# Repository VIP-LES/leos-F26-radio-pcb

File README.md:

# LEOS Radio PCB

This repository contains the KiCad schematic and PCB layout for the LEOS Radio PCB made fall 2026. The board integrates a Raspberry Pi Pico, an E22-900M30S LoRa radio module, and a CAN-FD interface.

The Raspberry Pi Pico communicates with the radio module through SPI1 and the MCP2518FD CAN-FD controller through SPI0. An MCP2562FD transceiver connects the CAN controller to the LEOS CAN bus. An SMA connector provides the connection for an external antenna.

## Board Overview
Main hardware functions:
- Wireless communication: E22-900M30S LoRa radio module provides wireless transmission and reception through an external antenna connected to the SMA connector.
- CAN-FD communication: MCP2518FD controller and MCP2562FD transceiver provide the interface to the LEOS CAN bus.
- Microcontroller control: Pico interfaces with the radio module and CAN controller through separate SPI buses. Additional GPIO connections provide radio reset, busy monitoring, interrupt, and receive-enable signals.

## Electrical Design
- Board supply: 5 V
- Microcontroller: Raspberry Pi Pico, as labeled in the schematic
- Radio module: E22-900M30S
- CAN-FD controller: MCP2518FD
- CAN-FD transceiver: MCP2562FD
- Bus connectors: Two four-pin MicroFit connectors

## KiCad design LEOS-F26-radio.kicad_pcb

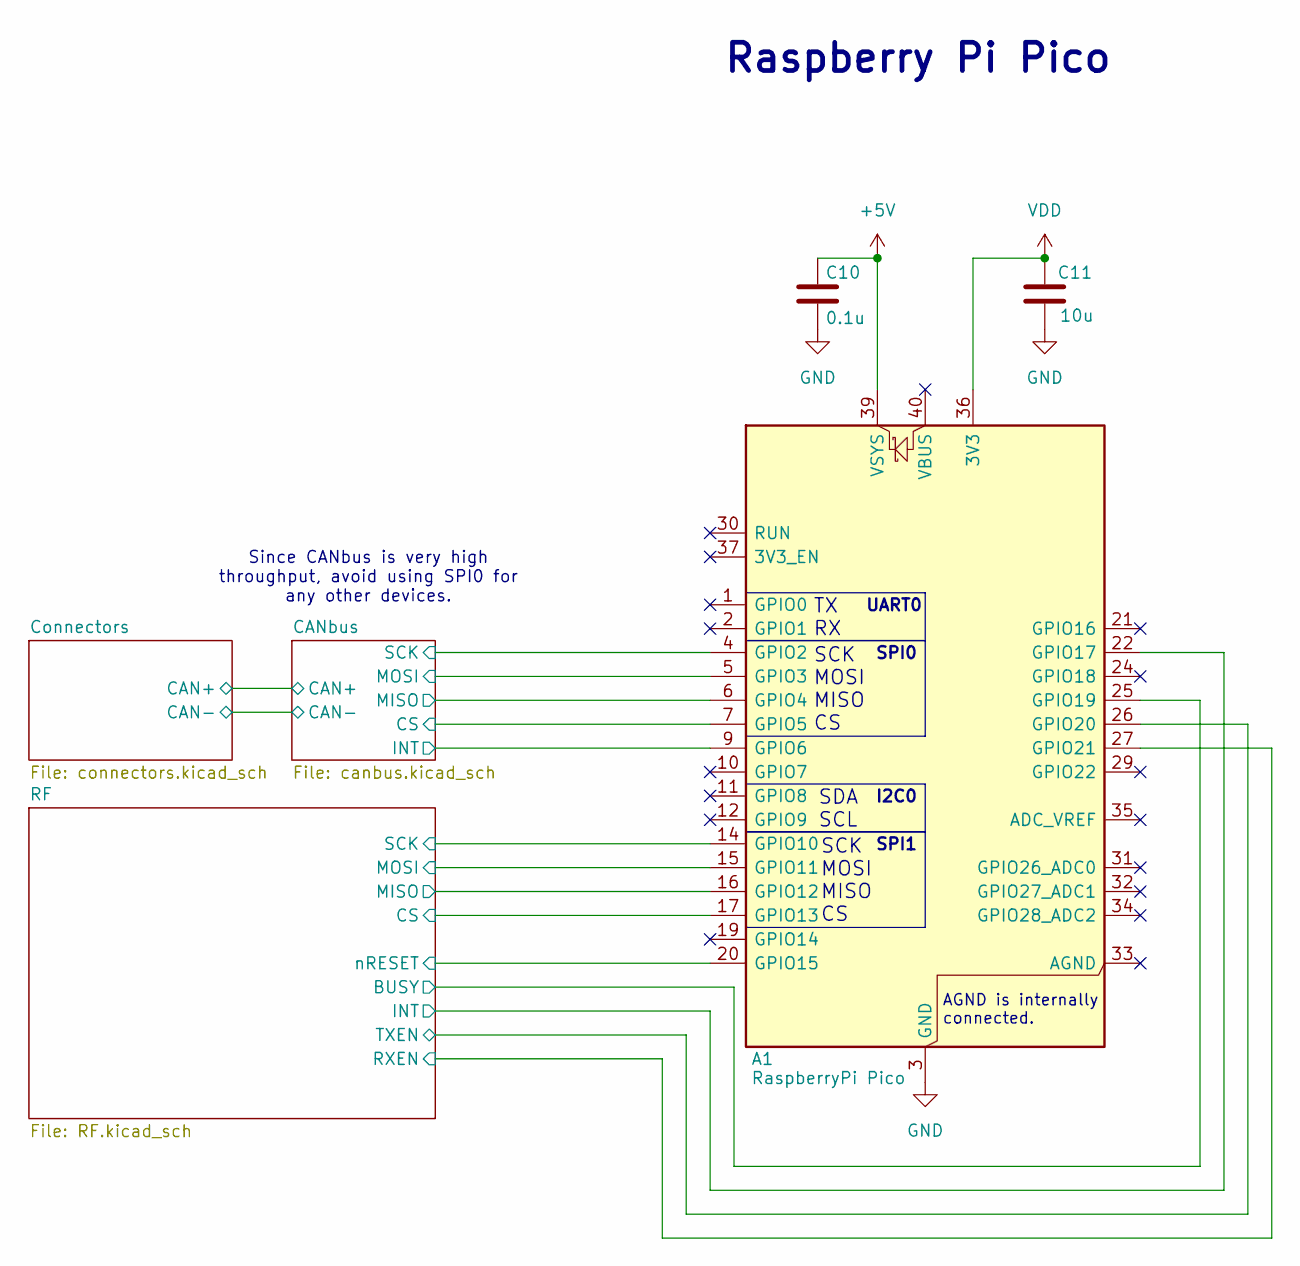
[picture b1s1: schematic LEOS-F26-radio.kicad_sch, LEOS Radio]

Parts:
A1: RaspberryPi Pico; RaspberryPi_Pico_Common_Unspecified; MPN PIM724; Digikey 1778-PIM724-ND
C10: 0.1u; C_0805_2012Metric; MPN CL21B104KBCNNNC; Digikey 1276-1003-1-ND
C11: 10u; C_0805_2012Metric; MPN CL21B106KOQNNNE; Digikey 1276-2872-1-ND

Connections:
+5V: A1.39 (VSYS), C10.1; also elsewhere on the board
/CANbus/CS: A1.7 (GPIO5); also elsewhere on the board
/CANbus/INT: A1.9 (GPIO6); also elsewhere on the board
/CANbus/MISO: A1.6 (GPIO4); also elsewhere on the board
/CANbus/MOSI: A1.5 (GPIO3); also elsewhere on the board
/CANbus/SCK: A1.4 (GPIO2); also elsewhere on the board
/RF/BUSY: A1.25 (GPIO19); also elsewhere on the board
/RF/CS: A1.17 (GPIO13); also elsewhere on the board
/RF/INT: A1.22 (GPIO17); also elsewhere on the board
/RF/MISO: A1.16 (GPIO12); also elsewhere on the board
/RF/MOSI: A1.15 (GPIO11); also elsewhere on the board
/RF/RXEN: A1.27 (GPIO21); also elsewhere on the board
/RF/SCK: A1.14 (GPIO10); also elsewhere on the board
/RF/TXEN: A1.26 (GPIO20); also elsewhere on the board
/RF/nRESET: A1.20 (GPIO15); also elsewhere on the board
GND: A1.3 (GND), A1.8 (GND), A1.13 (GND), A1.18 (GND), A1.23 (GND), A1.28 (GND), A1.38 (GND), C10.2, C11.2; also elsewhere on the board
VDD: A1.36 (3V3), C11.1; also elsewhere on the board

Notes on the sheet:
SPI1
Raspberry Pi Pico
SCK MOSI MISO CS
Since CANbus is very high throughput, avoid using SPI0 for any other devices.
SPI0
SDA SCL
TX RX
UART0
I2C0
AGND is internally connected.

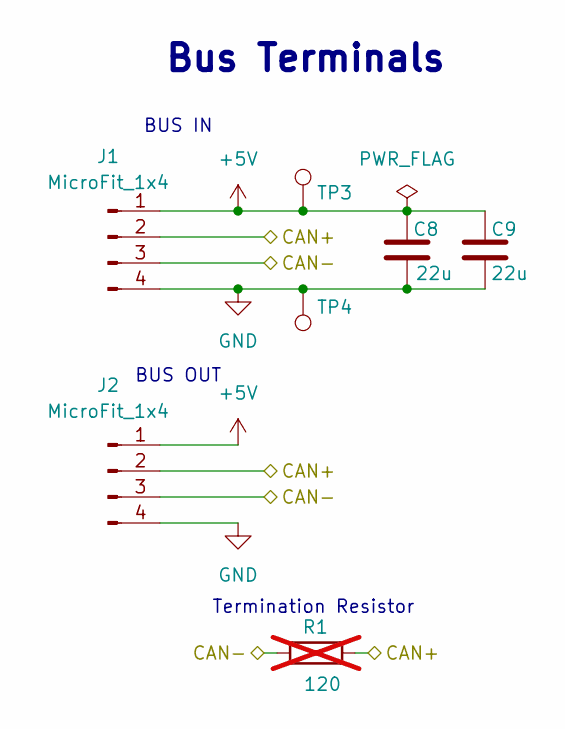
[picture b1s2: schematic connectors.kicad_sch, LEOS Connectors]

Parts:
C8, C9: 22u; C_1206_3216Metric; MPN CL31B226MPHNNNE; Digikey 1276-3148-1-ND
J1, J2: MicroFit_1x4; Molex_MicroFit3.0_43650-0410_1x04_Horizontal; MPN 0436500409; Digikey WM1882CT-ND
R1: 120; R_Axial_DIN0207_L6.3mm_D2.5mm_P7.62mm_Horizontal; MPN CF14JT120R; Digikey CF14JT120RCT-ND; not fitted
TP3: 5V Test Point; TestPoint_Loop_D2.60mm_Drill0.9mm_Beaded; MPN 5000; Digikey 36-5000-ND
TP4: GND Test Point; TestPoint_Loop_D2.60mm_Drill0.9mm_Beaded; MPN 5001; Digikey 36-5001-ND

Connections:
+5V: C8.1, C9.1, J1.1, J2.1, TP3.1 (1_1); also elsewhere on the board
/CANbus/CAN+: J1.2, J2.2, R1.2; also elsewhere on the board
/CANbus/CAN-: J1.3, J2.3, R1.1; also elsewhere on the board
GND: C8.2, C9.2, J1.4, J2.4, TP4.1 (1_1); also elsewhere on the board

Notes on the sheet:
BUS OUT
Bus Terminals
BUS IN
Termination Resistor

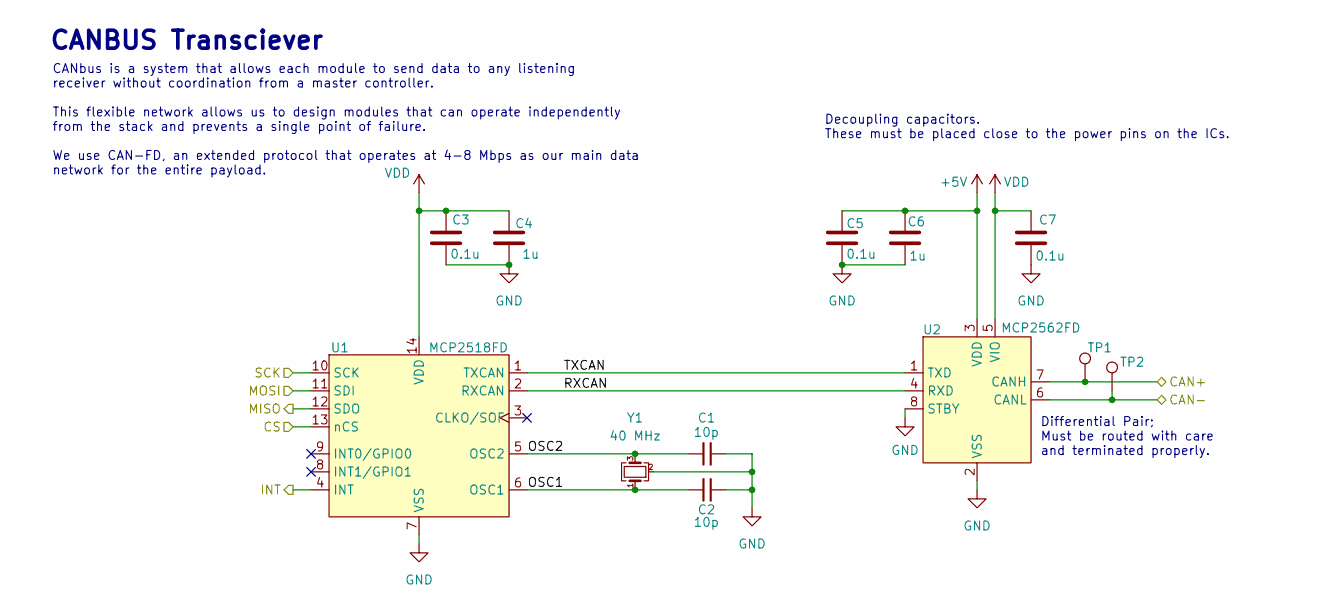
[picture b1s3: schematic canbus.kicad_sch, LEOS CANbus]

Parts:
C1, C2: 10p; C_0805_2012Metric; MPN CL21C100CBANNNC; Digikey 1276-2561-1-ND
C3, C5, C7: 0.1u; C_0805_2012Metric; MPN CL21B104KBCNNNC; Digikey 1276-1003-1-ND
C4, C6: 1u; C_0805_2012Metric; MPN C0805C105K3RACTU; Digikey 399-C0805C105K3RACTUCT-ND
TP1: CAN-H Test Point; TestPoint_Loop_D2.60mm_Drill0.9mm_Beaded; MPN 5004; Digikey 36-5004-ND
TP2: CAN-L Test Point; TestPoint_Loop_D2.60mm_Drill0.9mm_Beaded; MPN 5116; Digikey 36-5116-ND
U1: MCP2518FD; SOIC-14_3.9x8.7mm_P1.27mm; MPN MCP2518FDT-E/SL; LCSC C626758
U2: MCP2562FD; SOIC-8_3.9x4.9mm_P1.27mm; MPN MCP2562FDT-H/SN; LCSC C511335
Y1: 40 MHz; Crystal_SMD_2016-4Pin_2.0x1.6mm; MPN ECS-400-10-37B2-CKY-TR; Digikey 50-ECS-400-10-37B2-CKY-TRCT-ND

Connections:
+5V: C5.1, C6.1, U2.3 (VDD); also elsewhere on the board
/CANbus/CAN+: TP1.1 (1_1), U2.7 (CANH); also elsewhere on the board
/CANbus/CAN-: TP2.1 (1_1), U2.6 (CANL); also elsewhere on the board
/CANbus/CS: U1.13 (nCS); also elsewhere on the board
/CANbus/INT: U1.4 (INT); also elsewhere on the board
/CANbus/MISO: U1.12 (SDO); also elsewhere on the board
/CANbus/MOSI: U1.11 (SDI); also elsewhere on the board
/CANbus/OSC1: C2.2, U1.6 (OSC1), Y1.1
/CANbus/OSC2: C1.2, U1.5 (OSC2), Y1.3
/CANbus/RXCAN: U1.2 (RXCAN), U2.4 (RXD)
/CANbus/SCK: U1.10 (SCK); also elsewhere on the board
/CANbus/TXCAN: U1.1 (TXCAN), U2.1 (TXD)
GND: C1.1, C2.1, C3.2, C4.2, C5.2, C6.2, C7.2, U1.7 (VSS), U2.2 (VSS), U2.8 (STBY), Y1.2 (G), Y1.4 (G); also elsewhere on the board
VDD: C3.1, C4.1, C7.1, U1.14 (VDD), U2.5 (VIO); also elsewhere on the board

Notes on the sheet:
Differential Pair; Must be routed with care and terminated properly.
CANBUS Transciever
CANbus is a system that allows each module to send data to any listening receiver without coordination from a master controller. This flexible network allows us to design modules that can operate independently from the stack and prevents a single point of failure. We use CAN-FD, an extended protoco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
Decoupling capacitors. These must be placed close to the power pins on the ICs.

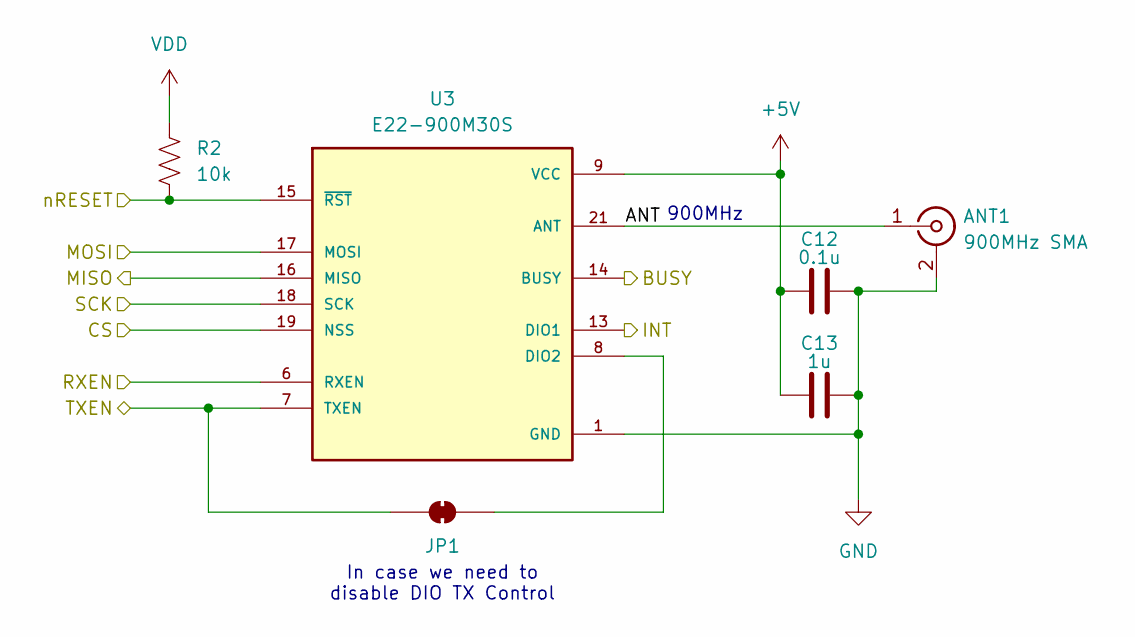
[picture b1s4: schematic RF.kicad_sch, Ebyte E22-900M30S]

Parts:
ANT1: 900MHz SMA; SMA_Molex_73251-1153_EdgeMount_Horizontal; MPN 0732511153; Digikey 900-0732511153-ND
C12: 0.1u; C_0805_2012Metric; MPN CL21B104KBCNNNC; Digikey 1276-1003-1-ND
C13: 1u; C_0805_2012Metric; MPN C0805C105K3RACTU; Digikey 399-C0805C105K3RACTUCT-ND
JP1: SolderJumper_2_Bridged; SolderJumper-2_P1.3mm_Bridged_RoundedPad1.0x1.5mm
R2: 10k; R_0805_2012Metric; MPN CRCW080510K0FKEA; Digikey 541-10.0KCCT-ND
U3: E22-900M30S; XCVR_E22-900M30S

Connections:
+5V: C12.1, C13.1, U3.9 (VCC), U3.10 (VCC); also elsewhere on the board
/RF/ANT: ANT1.1 (In), U3.21 (ANT)
/RF/BUSY: U3.14 (BUSY); also elsewhere on the board
/RF/CS: U3.19 (NSS); also elsewhere on the board
/RF/INT: U3.13 (DIO1); also elsewhere on the board
/RF/MISO: U3.16 (MISO); also elsewhere on the board
/RF/MOSI: U3.17 (MOSI); also elsewhere on the board
/RF/RXEN: U3.6 (RXEN); also elsewhere on the board
/RF/SCK: U3.18 (SCK); also elsewhere on the board
/RF/TXEN: JP1.1 (A), U3.7 (TXEN); also elsewhere on the board
/RF/nRESET: R2.2, U3.15 (~RST); also elsewhere on the board
GND: ANT1.2 (Ext), C12.2, C13.2, U3.1 (GND), U3.2 (GND), U3.3 (GND), U3.4 (GND), U3.5 (GND), U3.11 (GND), U3.12 (GND), U3.20 (GND), U3.22 (GND); also elsewhere on the board
unnamed: JP1.2 (B), U3.8 (DIO2)
VDD: R2.1; also elsewhere on the board

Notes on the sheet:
In case we need to disable DIO TX Control
900MHz

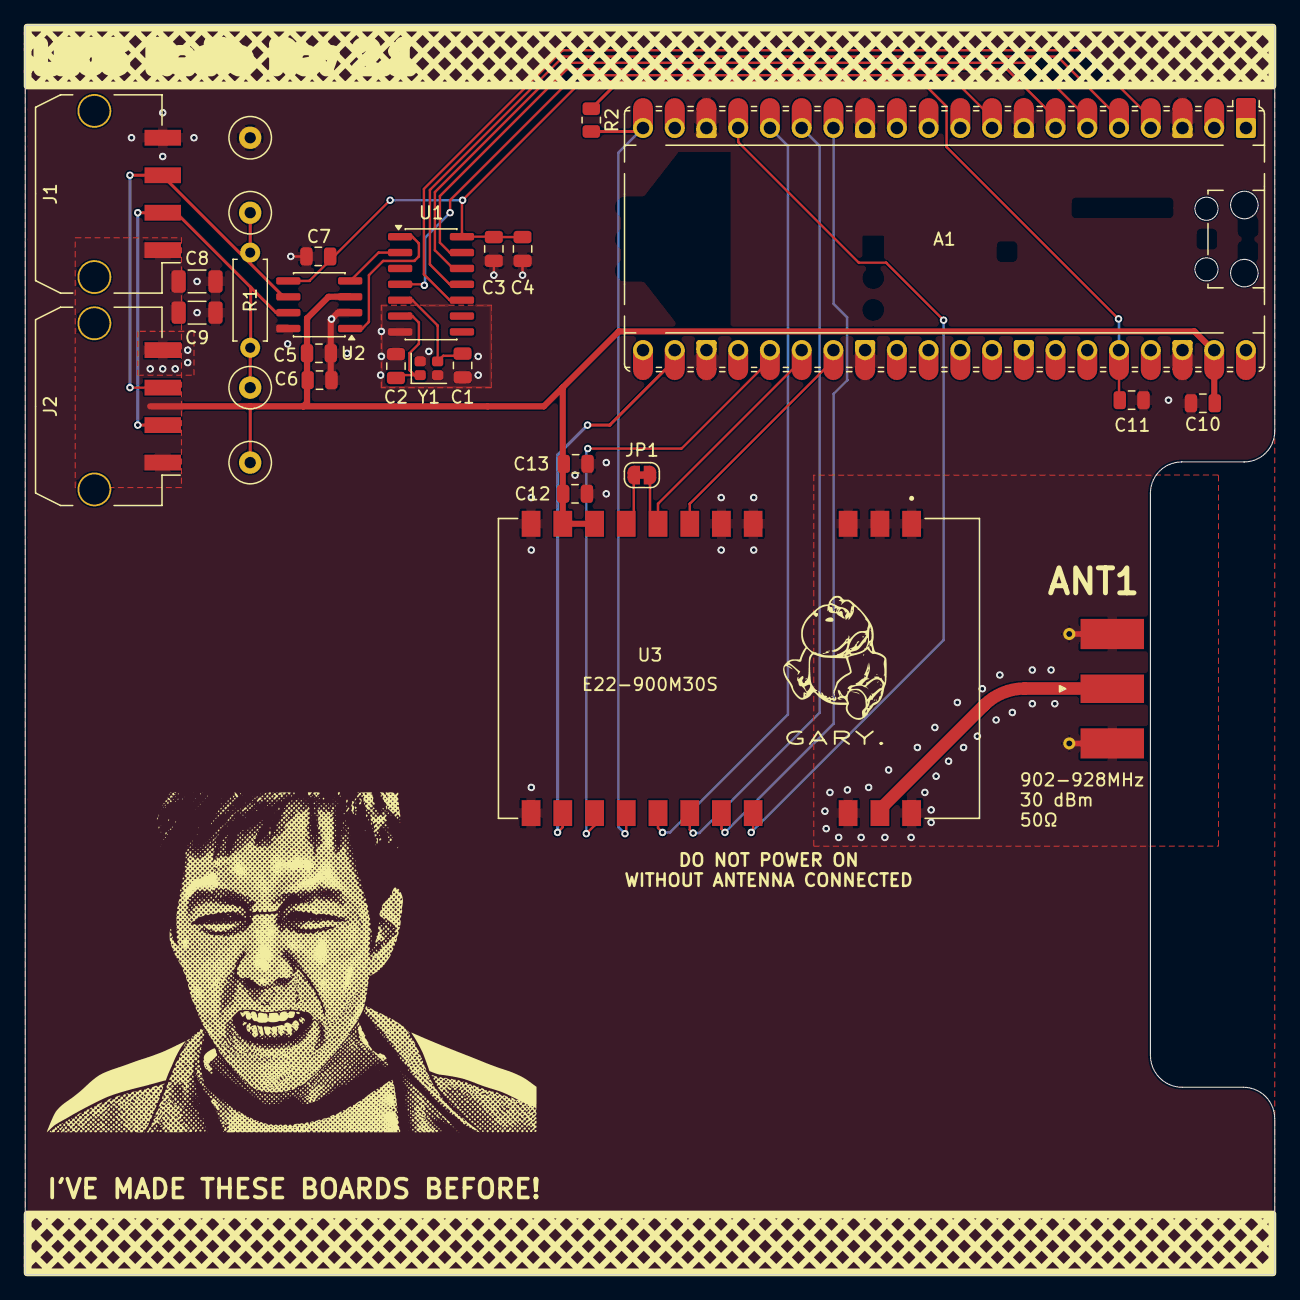
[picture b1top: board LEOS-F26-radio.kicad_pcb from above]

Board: 2 copper layers, 100.0 x 100.0 mm, 28 parts (0 on the bottom side), 25 nets.
